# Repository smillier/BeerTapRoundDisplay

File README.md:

# BeerTapRoundDisplay V2 - Remote Scale (ESP32-C6 + BLE)

Fork of [BeerTapRoundDisplay](https://github.com/smillier/BeerTapRoundDisplay) that separates the scale (HX711 + weight sensors) from the round GC9A01 display. The two boards communicate over Bluetooth Low Energy instead of being wired together on a single ESP32.

`display-esp32` targets an all-in-one **ESP32-C3 + 1.28" round GC9A01 touch display** module (sold on AliExpress under the PCB reference "JCZN ESP32-2424S012"), instead of a bare ESP32 wired to a separate GC9A01 breakout. Long-pressing the screen sends a tare command, same as the "Tare" button in the web UI.

**Jump to:** [Why two boards](#why-two-boards) · [Repo structure](#repo-structure) · [BLE protocol](#ble-protocol) · [scale-esp32c6](#scale-esp32c6-hx711-wiring) · [display-esp32](#display-esp32-display) · [Web UI](#web-ui-beetap-control) · [Security](#security) · [Flashing both boards](#flashing-both-boards) · [Limitations](#limitations--todo)

## Why two boards?

- The scale (HX711 + load cells) stays as close as possible to the keg, under its foot, far from the display, which is mounted remotely on the cabinet/fridge front panel.
- The ESP32-C6 is a natural fit for this node: small, cheap, native BLE, no need for Wifi/display/large flash on the scale side.
- The display keeps the existing Wifi/OTA/web server (beer config, IBU, ABV, SG...) and shows a status dot (green/orange/red) indicating how fresh the BLE link is.

## Repo structure

```
scale-esp32c6/     Scale firmware (HX711 -> BLE GATT server)
display-esp32/     Display firmware (BLE GATT client -> display + Wifi/webserver)
```

These are two independent PlatformIO projects, flashed separately (two `platformio.ini` files).

## BLE Protocol

The scale (`scale-esp32c6`) is the **BLE server (peripheral)**; the display (`display-esp32`) is the **BLE client (central)**. There's no pairing/bonding (no sensitive data is exchanged) — the connection is made by filtering on the service UUID.

| Element | UUID | Type | Content |
|---|---|---|---|
| Scale service | `a1f4e100-3b7a-4f56-9d1b-2f6a9c5e10a0` | - | - |
| Weight characteristic | `a1f4e101-3b7a-4f56-9d1b-2f6a9c5e11a0` | READ + NOTIFY | `float32` weight in grams |
| Command characteristic | `a1f4e102-3b7a-4f56-9d1b-2f6a9c5e12a0` | WRITE | `uint8`: `0x01` = tare |

These values are defined in `scale-esp32c6/include/config.h` and `display-esp32/include/config.h` (must stay identical on both sides).

Behavior:

- The scale measures weight every `WEIGHT_UPDATE_PERIOD_MS` (2s by default) and notifies the value if a client is connected.
- The display scans, connects to the first device advertising the service above, and automatically resubscribes on disconnection (`BLE_RECONNECT_PERIOD_MS`).
- Volume (weight / configured SG density on the display) is still computed on the display side, as before — the scale only reports raw weight.
- A "Tare" tap in the display's web UI (`POST /tare`) sends the command to the scale, which performs `scale.tare()`.
- `GET /scale_status` returns `{"connected":bool,"stale":bool}` for external monitoring.
- On the display, a dot at the top of the dial shows status: green = fresh data, orange = connected but stale data (> `BLE_WEIGHT_STALE_MS` = 15s), red = scale not connected.

## scale-esp32c6: HX711 wiring

| HX711 | ESP32-C6 |
|---|---|
| DOUT | GPIO2 |
| SCK | GPIO3 |
| VCC | 3.3V (or 5V depending on HX711 module) |
| GND | GND |

GPIO2/3 were chosen because GPIO4, 5, 8, 9, 15 are boot strapping pins on the ESP32-C6 and must be avoided. Adjust `SCALE_CALIBRATION_FACTOR` in `scale-esp32c6/include/config.h` for your own load cell (same calibration procedure as the original: weigh a known weight and adjust the factor).

`scale_setup()`/`scale_tare()`/`getWeight()` use `HX711::wait_ready_timeout()` (1s) instead of the library's plain `tare()`/`get_units()`, which otherwise block forever if the HX711 never pulls DOUT low (not wired yet, loose connection...). Without this guard, a disconnected load cell hangs `setup()` before BLE ever starts advertising - with it, the scale still comes up and reports `0.0`.

### Building scale-esp32c6 on Windows

This project uses the [pioarduino](https://github.com/pioarduino/platform-espressif32) platform fork (the official PlatformIO `espressif32` registry entry dropped Arduino framework support for ESP32-C6). Two Windows-specific gotchas:
- **Build from a native shell (cmd/PowerShell), not Git Bash/MSYS** - pioarduino's `idf_tools.py`/esptool install step explicitly refuses to run under MSYS ("MSys/Mingw is not supported").
- **Set the console to UTF-8 first** (`chcp 65001` in `cmd`/PowerShell, plus `$env:PYTHONIOENCODING="utf-8"`) - esptool's progress bar otherwise crashes PlatformIO's output relay under the default `cp1252` codepage.

## display-esp32: Display

Runs on an **ESP32-C3** all-in-one module with a built-in 1.28" round GC9A01 display and CST816 capacitive touch, everything on one small board/PCB (no separate breakout or wiring). Pins (see `display-esp32/include/config.h`):

| Function | Pin |
|---|---|
| TFT MOSI | GPIO7 |
| TFT SCLK | GPIO6 |
| TFT CS | GPIO10 |
| TFT DC | GPIO2 |
| TFT RST | not connected (module is reset over SPI) |
| TFT Backlight | GPIO3 |
| Touch SDA | GPIO4 |
| Touch SCL | GPIO5 |
| Touch RST | GPIO1 |
| Touch INT | GPIO0 |

The touch controller (CST816, I2C address `0x15`) is handled by `display-esp32/src/touch.cpp` using the [fbiego/CST816S](https://github.com/fbiego/CST816S) library: a **long-press** anywhere on the screen sends a tare command to the scale over BLE (a plain tap is deliberately ignored, so brushing the screen doesn't accidentally zero it).

The HX711 is no longer wired on this board (moved to `scale-esp32c6`).

### Web UI ("BeerTap Control")

`display-esp32/data/` (served over Wifi at the device's `http://<ip>/` or
`http://BeerTapDisplay.local/`) is a from-scratch dark/OLED-themed control panel,
implemented from a [Claude Design](https://claude.ai/design) mockup
("BeerTap Control", project `e4750120-6cf9-463d-8540-04c588b6e35e`) against the
device's real REST API - plain HTML/CSS/JS, no framework, no CDN dependency (system
fonts only, so it works with zero internet access, same as the rest of the device).
Replaces the previous jQuery + w3.css UI, which alone was ~330KB of the ~376KB
`data/` folder (mostly the bundled jQuery copy) - the new UI is a fraction of that.

| Home | Settings |
|---|---|
|  |  |

- **Home tab**: live weight + circular level gauge (colour-coded green→red, same
  spirit as the physical display's own ring meter), Tare button, "full keg" capacity
  estimate (used only to compute the gauge %), and the beer profile form (name, SG,
  IBU, EBC, ABV)
- **Settings tab**: Wifi status + Reset Wifi, firmware/filesystem OTA upload (via
  ElegantOTA's real `/ota/start` + `/ota/upload` API, with a progress bar), and a
  Restart button
- New backend endpoints added to `setup.cpp` to support it:
  - `GET /beer_profile` - JSON `{name, sg, ibu, ebc, abv, capacity}`, single read to
    populate the form (existing per-field `POST` endpoints are unchanged, used for
    saving)
  - `POST /beer_capacity` - same pattern as the existing per-field beer endpoints;
    backed by a new `getBeerCapacity()`/`setBeerCapacity()` pair in `config.cpp`
    (`Preferences`, default `19.0`) - the capacity estimate persists on the device
    like every other beer field, rather than only in the browser
  - `POST /restart` - `ESP.restart()` after a short delay so the response reaches
    the client first
  - `POST /reset_wifi` - clears saved Wifi credentials
    (`WiFiManager::resetSettings()`, wrapped as `resetWifiSettings()` in
    `wifi_setup.cpp` to keep `WiFiManager.h` out of `setup.cpp` - see the comment on
    `connectWifi()` about the `HTTP_GET`/`HTTP_POST` enum collision with
    ESPAsyncWebServer) then reboots into the `TapDisplay_AP` portal
  - The old `/param.xml` + `/wparamxml` routes (a stale, unsynced static XML file)
    were removed, superseded by `/beer_profile`

### Security

A penetration test of `display-esp32` found that every endpoint - including the web UI, the beer-profile API, `/tare`,
`/restart`, `/reset_wifi`, and most seriously the OTA firmware-upload path
(`/update`, `/ota/start`, `/ota/upload`) - had **no authentication of any kind**,
meaning anyone on the same network could silently reconfigure the device, reboot
it, wipe its Wifi settings, or push arbitrary firmware. This is now fixed:

- Every custom endpoint in `setup.cpp` and both OTA channels (ElegantOTA's web
  upload *and* the separate `ArduinoOTA` WiFi-upload protocol on port 8266) are
  gated behind a single shared username/password (HTTP Basic auth - `checkAuth()`
  in `setup.cpp`, username fixed as `admin`).
- The password is **not** a hardcoded default shipped in every device running
  this firmware - `getApiPassword()` (`config.cpp`) generates a random 12-character
  password per device on first boot (ESP32 hardware RNG, ambiguous characters like
  `I`/`l`/`1`/`O`/`0` excluded since it's read off a Serial console), persists it
  via `Preferences`, and `initialize()` prints it to Serial **on every boot** so
  it can always be retrieved with just a USB cable.
- `POST /api_password` (requires the *current* password) lets the owner set a
  memorable password from the web UI afterwards instead of living with the
  random one forever.
- First login after flashing this version: open a Serial monitor at 115200 baud,
  power-cycle the device, and look for the `Web UI / OTA login` block printed
  right after boot. The browser's native HTTP Basic Auth prompt will then accept
  that username/password for the web UI, and the same credentials work for
  ElegantOTA's `/update` page and for `pio run -t upload` over WiFi (`ArduinoOTA`).

## Flashing both boards

Each folder is a standalone PlatformIO project:

```bash
cd scale-esp32c6
pio run -t upload                     # ESP32-C6 over USB

cd ../display-esp32
pio run -e esp32-c3-usb -t upload     # ESP32-C3 firmware, first flash over USB
pio run -e esp32-c3-usb -t uploadfs   # ESP32-C3 filesystem image (data/ folder - web UI, beer BMPs)
pio run -e esp32-c3-ota -t upload     # subsequent firmware flashes over Wifi/OTA
                                       # (set upload_port in platformio.ini to the display's IP/hostname)
```

`display-esp32` keeps OTA (ArduinoOTA + ElegantOTA) as in the original project; `scale-esp32c6` is flashed over USB (no OTA, no Wifi on this board).

**The filesystem image (`uploadfs`) is required, not optional** - without it SPIFFS fails to mount, `initialize()` returns before ever calling `display_init()`, and the screen stays blank.

### Native-USB boards (JCZN ESP32-2424S012, ESP32-C6-DevKitM-1, clones): manual reset needed

Both boards talk USB through the chip's built-in USB-Serial/JTAG controller (no external CP210x/CH340 bridge), which has no reliable auto-reset circuit:
- **Entering bootloader mode** (before every `upload`/`uploadfs`): hold **BOOT**, tap **RESET** while still holding BOOT, then release BOOT.
- **Returning to normal run mode** (after every flash): a plain RESET tap is not reliable either - fully **unplug/replug the USB cable** to guarantee a clean boot into the app.
- **Opening a serial monitor can itself reset the board back into bootloader** (default DTR/RTS assertion on connect is misread as a reset request). If the monitor shows nothing at all right after a flash, reopen it with `pio device monitor -p COMx -b 115200 --rts 0 --dtr 0` before assuming the firmware is broken.

Hardware-verified on real boards (2026-07): `display-esp32` boots, connects to Wifi (falls back to the `TapDisplay_AP` WiFiManager captive portal if no credentials are saved), shows the beer dial, and long-press-to-tare over touch. `scale-esp32c6` advertises over BLE, the display connects (status dot green), and the tare command round-trips correctly (`Tare requested by display` logged on the scale on each long-press) - tested without load cells physically wired.

## Limitations / TODO

- The `Case/` and `PCB/` files from the original repo (3D enclosure, Eagle PCB) were designed for the combined display+HX711 board: they'll need to be redesigned/split into two enclosures (not addressed in this version, out of software scope).
- No BLE pairing (LE Secure Connections): fine for home use where only weight is transmitted, but worth keeping in mind if the protocol evolves.

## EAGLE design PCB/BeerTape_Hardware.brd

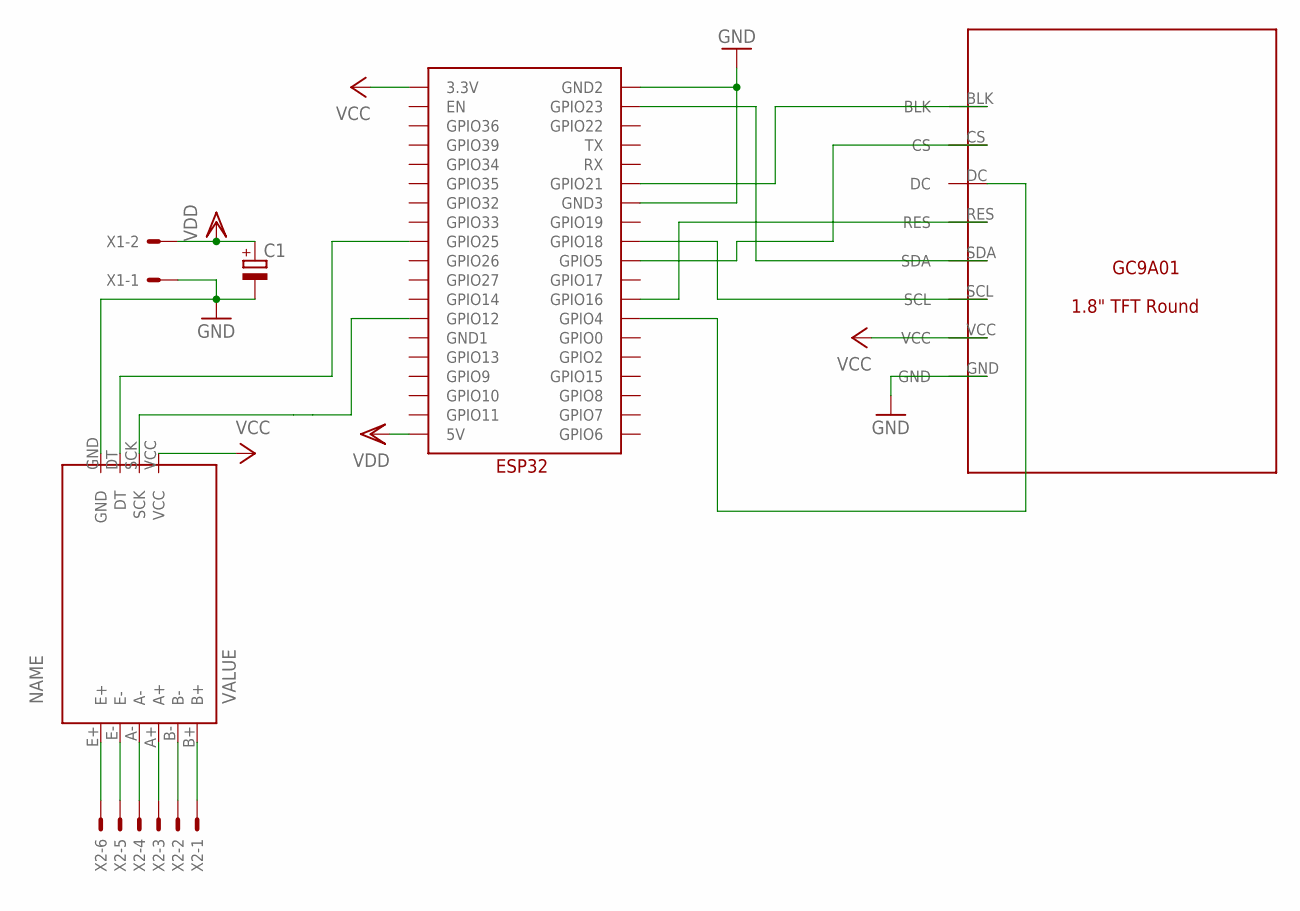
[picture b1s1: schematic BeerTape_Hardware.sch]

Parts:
C1: CPOL-EUE2,5-6E; E2,5-6E
HX711: HX711
U$1: GC9A01
U$2: ESP32
X1: KK-156-2
X2: 22-23-2061

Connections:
GND: C1.-, HX711.GND, U$1.GND, U$2.GND2, U$2.GND3, X1.1
unnamed: U$1.DC, U$2.GPIO4
unnamed: U$1.SDA, U$2.GPIO23
unnamed: U$1.BLK, U$2.GPIO21
unnamed: U$1.SCL, U$2.GPIO18
unnamed: U$1.RES, U$2.GPIO16
unnamed: U$1.CS, U$2.GPIO5
unnamed: HX711.SCK, U$2.GPIO12
unnamed: HX711.DT, U$2.GPIO25
unnamed: HX711.E+, X2.6
unnamed: HX711.E-, X2.5
unnamed: HX711.A-, X2.4
unnamed: HX711.A+, X2.3
unnamed: HX711.B-, X2.2
unnamed: HX711.B+, X2.1
VCC: HX711.VCC, U$1.VCC, U$2.3.3V
VDD: C1.+, U$2.5V, X1.2

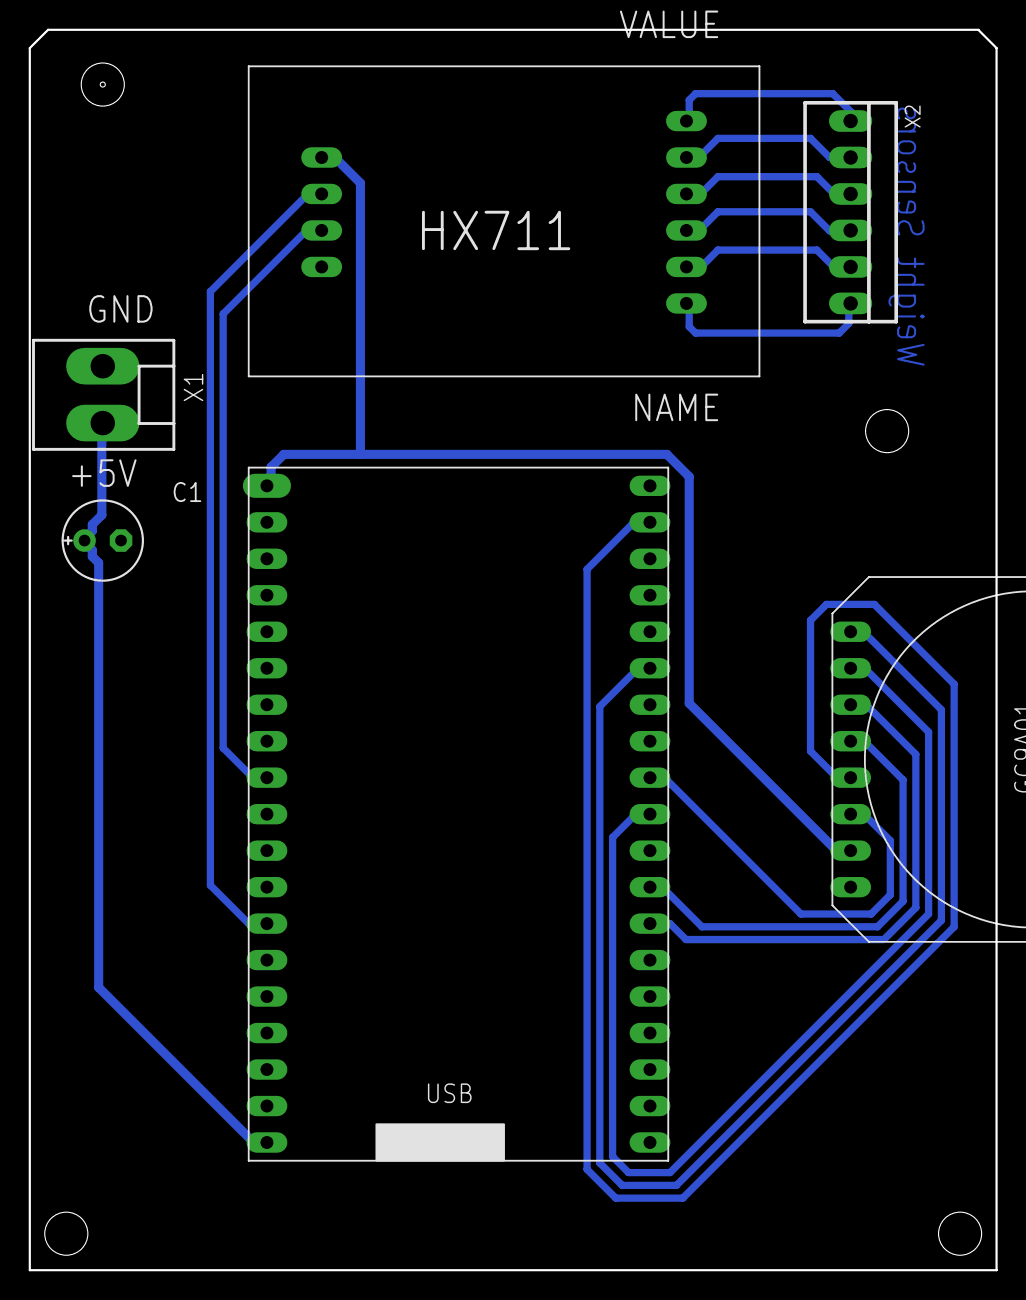
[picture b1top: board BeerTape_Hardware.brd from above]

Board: 2 copper layers, 67.3 x 86.4 mm, 6 parts (0 on the bottom side), 17 nets.

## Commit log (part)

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2021-11-12 initialisation
2021-11-12 add doc
2021-11-12 Add SPIFFS Images support for beer color
2022-02-24 Add Case stl for 3D printer
2022-02-24 Edit
2022-02-24 Add Hx711 Sensors
2022-02-27 Add quick electronic schema
2022-03-01 Add Autodesk Eagle PCB files
2022-03-01 Add PCB picture
2022-03-11 Refactoring
2022-03-11 Add weight measurement classes
2022-03-11 Add weight function and display
2022-03-11 Add weight function
2022-03-12 Code cleanup
2022-03-20 Extern class for display
2022-04-30 Progress on weight scale - Not fully functionnal
2022-05-01 Weight measure
2022-06-11 PCB tested OK
2022-06-11 Add PCB images
2022-06-11 adjustements
2022-06-22 Add real screen installation
2022-06-23 Code corrections for first tests
2022-06-23 Add serial monitoring speed
2022-06-24 **FOR BACKUP ONLY** DO NOT USE OR TRY
2022-06-26 Add webserver and dynamic display updates
2022-06-27 Display optimization and code cleanup
2022-06-28 little update on werbserver
2022-06-28 Little update on html
2022-06-29 Add files
2022-06-29 Documentation
2022-06-29 Delete
2022-06-29 Update doc
2022-07-04 Preparing for new webserver
2022-07-04 Preparing for new web server
